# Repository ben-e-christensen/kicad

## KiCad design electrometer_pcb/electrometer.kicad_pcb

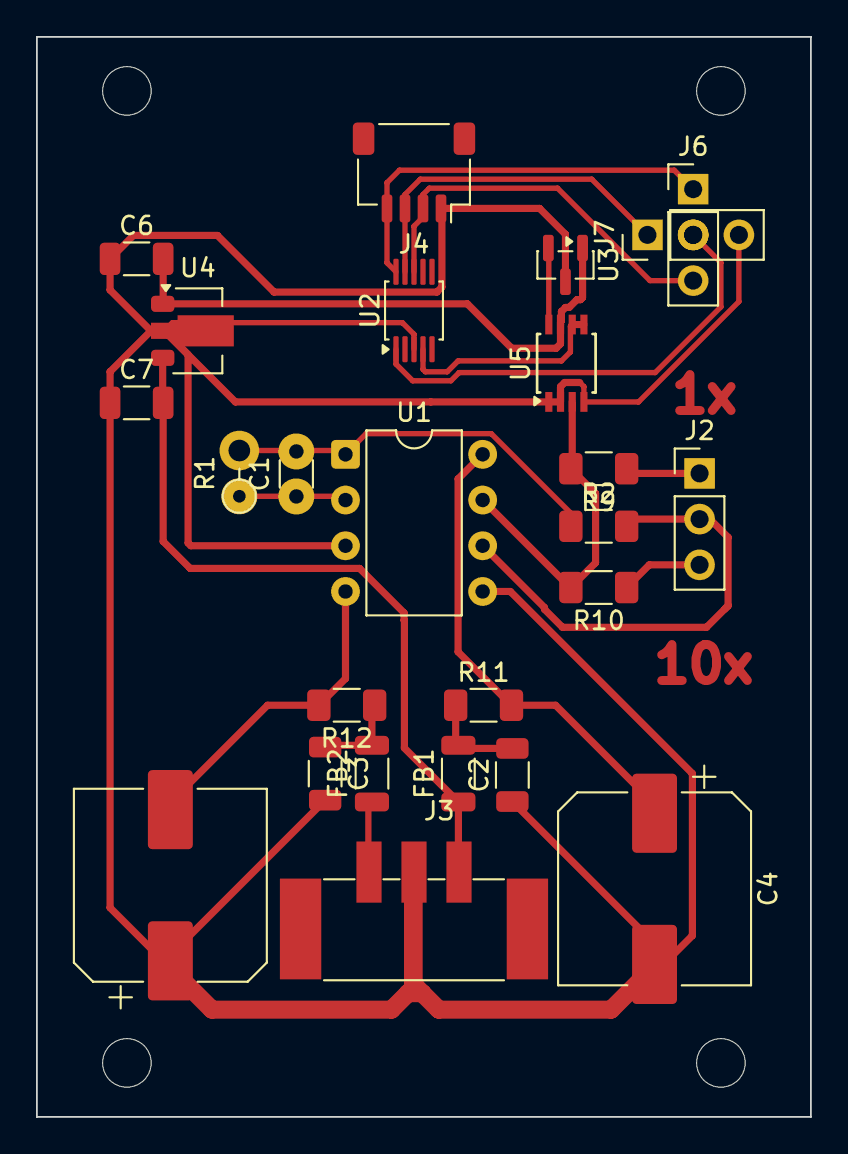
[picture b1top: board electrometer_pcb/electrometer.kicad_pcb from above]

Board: 2 copper layers, 43.0 x 60.0 mm, 25 parts (0 on the bottom side), 20 nets.

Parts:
C1: 100p; C_Disc_D3.0mm_W1.6mm_P2.50mm
C2, C3, C6, C7: 100n; C_1206_3216Metric
C4, C5: C_Polarized; CP_Elec_10x10.5
FB1, FB2: FerriteBead; L_1206_3216Metric
J2, J6, J7: Conn_01x03_Pin; PinHeader_1x03_P2.54mm_Vertical
J3: Screw_Terminal_01x03; TerminalBlock_Phoenix_PTSM-0,5-3-2,5-V-SMD_1x03-1MP_P2.50mm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
J4: PRT-14417; JST_SH_SM04B-SRSS-TB_1x04-1MP_P1.00mm_Horizontal
R1: 5G; R_Axial_DIN0204_L3.6mm_D1.6mm_P2.54mm_Vertical
R2, R9: 1k; R_1206_3216Metric_Pad1.30x1.75mm_HandSolder
R10: 10k; R_1206_3216Metric_Pad1.30x1.75mm_HandSolder
R11, R12: 10; R_1206_3216Metric_Pad1.30x1.75mm_HandSolder
U1: LMC6082; DIP-8_W7.62mm
U2: ADS1115IDGS; TSSOP-10_3x3mm_P0.5mm
U3: REF3025; SOT-23
U4: 5V LDO; SOT-89-3
U5: INA159AIDGKR; TSSOP-8_3x3mm_P0.65mm

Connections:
+2V5: U3.2 (OUT), U5.8 (REF_2)
+3.3V: J4.2, J6.3, U2.8 (VDD)
+5V: C6.2, U3.1 (IN), U4.1 (OUT), U5.7 (V+)
/ADDR: J6.2, J7.2, U2.1 (ADDR)
/Blue: J4.3, J7.1, U2.9 (SDA)
/Output: R9.2, R10.2, U1.7, U5.3 (+IN)
/Yellow: J4.4, J6.1, U2.10 (SCL)
GND: C2.1, C3.2, C4.2, C5.1, C6.1, C7.1, J3.2, J4.1, J7.3, U1.3 (+), U1.5 (+), U2.3 (GND), U3.3 (GND), U4.2 (GND), U5.1 (REF_1), U5.2 (-IN), U5.4 (V-)
unnamed: C1.2, R1.2, R2.1, U1.1
unnamed: C2.2, FB1.2, R11.1
unnamed: C3.1, FB2.2, R12.1
unnamed: J2.1, R9.1
unnamed: J2.2, R2.2, U1.6 (-)
unnamed: J2.3, R10.1
unnamed: C1.1, R1.1, U1.2 (-)
unnamed: C4.1, R11.2, U1.8 (V+)
unnamed: C5.2, R12.2, U1.4 (V-)
unnamed: U2.4 (AIN0), U5.5 (SENSE), U5.6 (OUT)
V+: C7.2, FB1.1, J3.1, U4.3 (IN)
V-: FB2.1, J3.3

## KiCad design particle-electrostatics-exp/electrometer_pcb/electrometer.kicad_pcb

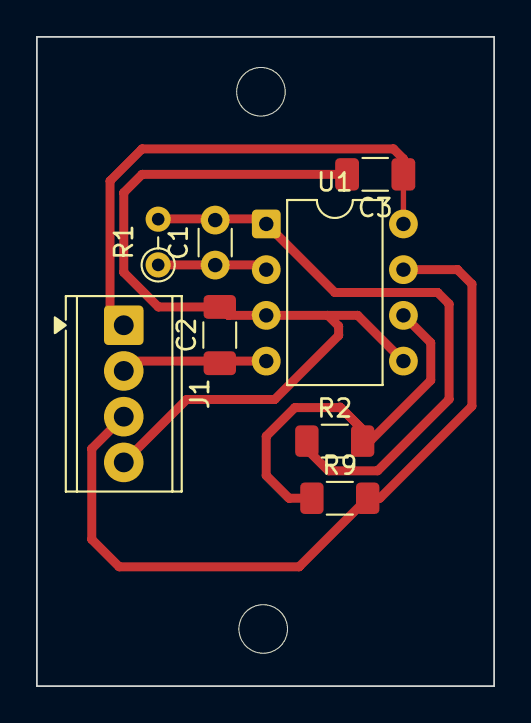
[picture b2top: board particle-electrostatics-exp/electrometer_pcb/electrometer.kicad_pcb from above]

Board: 2 copper layers, 25.4 x 36.1 mm, 8 parts (0 on the bottom side), 7 nets.

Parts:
C1: 1n; C_Disc_D3.0mm_W1.6mm_P2.50mm
C2, C3: 100n; C_1206_3216Metric_Pad1.33x1.80mm_HandSolder
J1: Screw_Terminal_01x04; TerminalBlock_Phoenix_MPT-0,5-4-2.54_1x04_P2.54mm_Horizontal
R1: 5M; R_Axial_DIN0204_L3.6mm_D1.6mm_P2.54mm_Vertical
R2, R9: 1k; R_1206_3216Metric_Pad1.30x1.75mm_HandSolder
U1: LMC6082; DIP-8_W7.62mm

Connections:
+9V: C3.1, J1.1
-9V: C2.1, J1.2
GND: C2.2, C3.2, J1.4, U1.3 (+), U1.5 (+)
unnamed: C1.2, R1.2, R2.1, U1.1
unnamed: J1.3, R9.2, U1.7
unnamed: C1.1, R1.1, U1.2 (-)
unnamed: R2.2, R9.1, U1.6 (-)
